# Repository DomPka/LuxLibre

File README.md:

<!-- SPDX-License-Identifier: CC-BY-SA-4.0 -->
<picture>
  <source media="(prefers-color-scheme: dark)" srcset="docs/img/luxlibre_banner_dark.png">
  
</picture>

# LuxLibre

<p align="center"><b>
<a href="#pick-a-light">Pick a light</a> &nbsp;·&nbsp;
<a href="docs/comparison.md">Compare</a> &nbsp;·&nbsp;
<a href="#in-your-browser">Web apps</a> &nbsp;·&nbsp;
<a href="docs/firmware/README.md">Firmware</a> &nbsp;·&nbsp;
<a href="docs/README.md">Design your own</a> &nbsp;·&nbsp;
<a href="hardware/flashka-keychain-v07/FlashKa_v0.7_Build_Guide.pdf">Build a FlashKa</a> &nbsp;·&nbsp;
<a href="#repository-map">Repository map</a> &nbsp;·&nbsp;
<a href="CONTRIBUTING.md">Help</a>
</b></p>

**Open-source flashlights, from the first requirement to the finished light.** LuxLibre is one firmware for many
lights, a set of design rules, a guide to choosing parts and testing them, and seven reference designs: the FlashKa
keychain light and the EDCO family of sealed everyday-carry lights. Every design comes with CAD, dimensioned
drawings, renders, a firmware board header and simulated light output. Anyone may build, change and sell lights
made with it, companies included ([LICENSING.md](LICENSING.md)).

## Pick a light

<picture>
  <source media="(prefers-color-scheme: dark)" srcset="docs/img/lineup_dark.png">
  
</picture>

*All seven at true scale (render). The [web site](https://dompka.github.io/LuxLibre/) has the same lineup: pick a
light there to see its details.*

<table>
<tr>
<td width="33%" valign="top">

<h3><a href="hardware/flashka-keychain-v07/README.md">FlashKa v0.7</a></h3>
<b>Keychain light with a laser and a Bluetooth presenter mode.</b><br>
99.2 × 20 × 18 mm · one 14500<br>
about 1,045 lm · 162 m throw · 2 h 17 min from turbo<br>
<sub><a href="hardware/flashka-keychain-v07/FlashKa_v0.7_Build_Guide.pdf">build guide</a> · <a href="hardware/flashka-keychain-v07/cad/FlashKa_tray_drawing.pdf">drawings</a> · <a href="https://dompka.github.io/LuxLibre/flashka/flashka-app.html">web app</a></sub>
</td>
<td width="33%" valign="top">

<h3><a href="hardware/edco-prism/README.md">EDCO Prism</a></h3>
<b>A beam that is white or any colour.</b><br>
Ø28 × 83 mm · one 18350<br>
about 1,250 lm turbo · red, green, blue and any mix<br>
<sub><a href="hardware/edco-prism/cad/EDCO_Prism_body_drawing.pdf">drawing</a> · <a href="hardware/edco-prism/cad/">CAD</a> · <a href="https://dompka.github.io/LuxLibre/luxlibre/">settings page</a></sub>
</td>
<td width="33%" valign="top">

<h3><a href="hardware/edco-mini/README.md">EDCO Mini</a></h3>
<b>Sealed keychain light with red and UV side lights.</b><br>
Ø22 × 73.5 mm (16340) or Ø19 × 69.4 mm<br>
about 950 lm · keyring tab · magnet version<br>
<sub><a href="hardware/edco-mini/cad/EDCO_Mini-16_body_drawing.pdf">drawings</a> · <a href="hardware/edco-mini/cad/">CAD</a> · <a href="firmware/boards/edco-mini-16/board.h">firmware</a></sub>
</td>
</tr>
<tr>
<td width="33%" valign="top">

<h3><a href="hardware/edco-v02/README.md">EDCO v0.2</a></h3>
<b>The bright one: an SST-40 at up to 5.7 A.</b><br>
Ø26 × 97.8 mm (18500) or Ø22 × 95.6 mm (14500)<br>
about 1,760 lm · USB-C under a twist collar<br>
<sub><a href="hardware/edco-v02/cad/EDCO-18_body_drawing.pdf">drawings</a> · <a href="hardware/edco-v02/cad/">CAD</a> · <a href="firmware/boards/edco-v02-18/board.h">firmware</a></sub>
</td>
<td width="33%" valign="top">

<h3><a href="hardware/edco-v01/README.md">EDCO v0.1</a></h3>
<b>A plain sealed tube with USB-C in the tail.</b><br>
Ø20 × 93.5 mm · one 14500<br>
about 966 lm · 2 h 21 min from turbo<br>
<sub><a href="hardware/edco-v01/cad/EDCO_body_drawing.pdf">drawing</a> · <a href="hardware/edco-v01/cad/">CAD</a> · <a href="firmware/boards/edco-v01/board.h">firmware</a></sub>
</td>
<td width="33%" valign="top">
<a href="docs/comparison.md"><picture><source media="(prefers-color-scheme: dark)" srcset="docs/img/compare_light_dark.png"></picture></a>
<h3><a href="docs/comparison.md">Compare them</a></h3>
<b>Every design against 14 popular lights</b>, from the RovyVon A3 Pro to the Fenix PD36R Pro: light, throw,
runtime, size and price, with sources.
</td>
</tr>
</table>

*Every picture is a render made from the design files. None of these lights has been built yet: every light figure
is simulated with the LuxLibre simulator (out of the front, LED at 85 °C) or estimated, and every page says
which.*

## Where to go next

| I want to | Go to |
|---|---|
| see how the designs compare with lights I can buy | [docs/comparison.md](docs/comparison.md) |
| look at a design in detail: specifications, renders, how it is built, cost, open points | the design pages above, or [all the lights](hardware/README.md) |
| get drawings and CAD to make parts | each design's `cad/` folder: STEP files and A3 drawings (DXF, PDF, PNG), e.g. [EDCO Prism](hardware/edco-prism/cad/README.md), [FlashKa v0.7](hardware/flashka-keychain-v07/cad/README.md) |
| try the FlashKa control app without a light | the [FlashKa web app](https://dompka.github.io/LuxLibre/flashka/flashka-app.html), *Try demo mode* |
| change the settings of a LuxLibre light from the browser | the [LuxLibre settings page](https://dompka.github.io/LuxLibre/luxlibre/) (Web Serial over USB-C; demo mode without a light) |
| run the firmware without hardware | [Quick start](#quick-start) and [docs/firmware/simulator.md](docs/firmware/simulator.md) |
| design my own light | [docs/README.md](docs/README.md): requirement sheet, choosing parts, design rules, testing |
| put LuxLibre on my board | [docs/firmware/porting.md](docs/firmware/porting.md) |
| build a FlashKa | the [build guide](hardware/flashka-keychain-v07/FlashKa_v0.7_Build_Guide.pdf) and [order files](hardware/flashka-keychain-v07/order_files/README.txt) |
| report a build, measurements or a problem | [CONTRIBUTING.md](CONTRIBUTING.md) and the [build report form](https://github.com/DomPka/LuxLibre/issues/new?template=build_report.yml) |

## The lights at a glance

| Light | Size (mm) | Cell | Light at 30 s | After 10 min | Throw | From turbo to the end point | What sets it apart |
|---|---|---|---|---|---|---|---|
| [FlashKa v0.7](hardware/flashka-keychain-v07/README.md) | 99.2 × 20 × 18 | 14500, 1,500 mAh | 966 lm | about 280 lm | 6,605 cd, 162 m | 2 h 17 min | Class 2 laser, Bluetooth presenter mode, glowing key ring |
| [EDCO Prism](hardware/edco-prism/README.md) | Ø28 × 83.0 | 18350, 1,200 mAh | 1,248 lm | about 280-350 lm | about 3,000 cd (est.) | 1 h 29 min | colour beam, RGB-lit button, settings page over USB-C |
| [EDCO Mini-16](hardware/edco-mini/README.md) | Ø22 × 73.5 | 16340, 650 mAh | 944 lm | about 230 lm | about 11,000 cd (est.) | 1 h 07 min | red and UV side lights, keyring tab, magnets in the M version |
| [EDCO Mini-14](hardware/edco-mini/README.md) | Ø19 × 69.4 | 14350 made to order, about 400 mAh | 978 lm | about 195 lm | about 5,600 cd (est.) | 51 min | the smallest; needs a cell made to order |
| [EDCO-18](hardware/edco-v02/README.md) | Ø26 × 97.8 | 18500, 1,500 mAh | 1,759 lm | about 330-390 lm | about 18,000 cd (est.) | 1 h 39 min | the brightest; USB-C under a twist collar |
| [EDCO-14](hardware/edco-v02/README.md) | Ø22 × 95.6 | 14500, 1,000 mAh | 1,561 lm | about 260-320 lm | about 11,000 cd (est.) | 1 h 18 min | the same in a slimmer body |
| [EDCO v0.1](hardware/edco-v01/README.md) | Ø20 × 93.5 | 14500, 1,500 mAh | 966 lm | about 290 lm | 6,605 cd, 162 m | 2 h 21 min | sealed USB-C socket in the tail |

All figures are simulated, out of the front, with the LED at 85 °C in 25 °C still air. "est." marks an estimate
from the optic's beam angle. The end point is ANSI FL1: 10 % of the 30 s output.

## Against popular flashlights

<picture>
  <source media="(prefers-color-scheme: dark)" srcset="docs/img/compare_light_dark.png">
  
</picture>

* **Keychain size.** The EDCO Mini gives more than twice the light of a 60 mm RovyVon A3 Pro at 30 s. The best
  16340 lights, the Olight Baton 4 and Fenix E18R V2.0, are shorter and still brighter.
* **14500 and 18350 size.** EDCO-18 and EDCO-14 are the brightest at 30 s and run the longest from turbo, but
  they are about 17-20 mm longer than the Skilhunt MiX-7 or Emisar D3AA.
  * EDCO Prism gives about 10 % less white than the MiX-7, the only other colour-beam light of its size. It runs
    longer and charges from any USB-C cable.
* **18650 size** is still the territory of lights like the Fenix PD36R Pro: no LuxLibre design is that big yet.

Every number, its source and what was left out: [docs/comparison.md](docs/comparison.md). The other lights were
measured by independent reviewers; the LuxLibre lights are simulated, and their measured numbers will replace these
once they are built.

## In your browser

| Page | What it does | Needs |
|---|---|---|
| **[LuxLibre settings page](https://dompka.github.io/LuxLibre/luxlibre/)** | reads and changes every parameter of a LuxLibre light over USB-C (Web Serial), and for the EDCO Prism the beam's colour and the custom colour; a demo mode with the EDCO Prism's settings | Chrome or Edge on a computer and a USB-C data cable |
| **[FlashKa control app](https://dompka.github.io/LuxLibre/flashka/flashka-app.html)** | battery, temperature and runtime; light on and off, levels and exact current; profiles with an editor; presenter settings and paired computers; a demo mode with a simulated light | Chrome or Edge on Android, Windows, macOS or ChromeOS; Bluefy on iPhone and iPad |
| **[FlashKa firmware installer](https://dompka.github.io/LuxLibre/flashka/flashka-flasher.html)** | writes the firmware through the light's USB-C port and checks what it wrote; the firmware image is inside the page | Chrome or Edge on a computer and a USB-C data cable |

All three run entirely in the browser: nothing is uploaded and there is no account. The
[start page](https://dompka.github.io/LuxLibre/) links them all. They are published from [site/](site/) and
[hardware/flashka-keychain-v06/app/](hardware/flashka-keychain-v06/app/) with GitHub Pages.

## Repository map

| Folder | What is in it | Start with |
|---|---|---|
| [hardware/](hardware/README.md) | the lights: design pages, CAD and drawings, renders, circuit boards, order files | [the lights](hardware/README.md) |
| &nbsp;&nbsp;[flashka-keychain-v07/](hardware/flashka-keychain-v07/README.md) | FlashKa v0.7, the keychain light with a laser and a presenter mode | [build guide](hardware/flashka-keychain-v07/FlashKa_v0.7_Build_Guide.pdf), [drawings](hardware/flashka-keychain-v07/cad/README.md) |
| &nbsp;&nbsp;[edco-prism/](hardware/edco-prism/README.md) | EDCO Prism, white or any-colour beam | [drawing](hardware/edco-prism/cad/README.md), [pictures](hardware/edco-prism/assets/README.md) |
| &nbsp;&nbsp;[edco-mini/](hardware/edco-mini/README.md) | EDCO Mini-16 and Mini-14, sealed keychain lights | [drawings](hardware/edco-mini/cad/README.md), [pictures](hardware/edco-mini/assets/README.md) |
| &nbsp;&nbsp;[edco-v02/](hardware/edco-v02/README.md) | EDCO-18 and EDCO-14, about 1,760 lm | [drawings](hardware/edco-v02/cad/README.md), [pictures](hardware/edco-v02/assets/README.md) |
| &nbsp;&nbsp;[edco-v01/](hardware/edco-v01/README.md) | EDCO v0.1, the first EDCO | [drawing](hardware/edco-v01/cad/README.md), [pictures](hardware/edco-v01/assets/README.md) |
| &nbsp;&nbsp;[flashka-keychain-v06/](hardware/flashka-keychain-v06/README.md), [v05/](hardware/flashka-keychain-v05/README.md) | older FlashKa designs; v0.6 also holds the FlashKa firmware and web pages | |
| &nbsp;&nbsp;[tools/](hardware/tools/README.md) | scripts for the drawings, animations, lineup and banner | |
| [firmware/](firmware/README.md) | the LuxLibre firmware source: core, ports, board headers, tests, simulator | [firmware guide](docs/firmware/README.md), [board headers](firmware/boards/README.md) |
| [docs/](docs/README.md) | design rules, choosing parts, flashlight types, testing, the comparison, the firmware guide | [reading paths](docs/README.md) |
| [tools/](tools/README.md) | `lux_calc.py` (runtime, throw, heat, trace width, NTC...) and the comparison charts | |
| [templates/](templates/README.md) | requirement sheet, design log, decision matrix, BOM, review checklist, test report | [requirement sheet](templates/requirements.md) |
| [site/](site/README.md) | the web site: start page and LuxLibre settings page | [live site](https://dompka.github.io/LuxLibre/) |

At the top level: [CHANGELOG](CHANGELOG.md), [CONTRIBUTING](CONTRIBUTING.md), [SAFETY](SAFETY.md),
[SECURITY](SECURITY.md), [LICENSING](LICENSING.md) (what the licences mean), [TRADEMARKS](TRADEMARKS.md) and the
[licence texts](LICENSES/). Every page has a path at the top (LuxLibre › Lights › EDCO Prism) to find your way back.

## Quick start

**Try the web pages without a light:** open the
[settings page](https://dompka.github.io/LuxLibre/luxlibre/) or the
[FlashKa control app](https://dompka.github.io/LuxLibre/flashka/flashka-app.html) and choose the demo mode.

**Try the LuxLibre firmware without hardware** (Linux, macOS, or Windows with WSL):

```sh
cd firmware
make test                                    # unit and behaviour tests
make sim BOARD=edco-prism                    # the simulator with the EDCO Prism's board header
build/luxsim-edco-prism --preset board "2C W600000"            # double click for turbo, then 10 minutes
build/luxsim-edco-prism --preset board "5C W2000 2C W2000"     # colour beam on, then the next colour
make sim BOARD=edco-mini-16                  # the same for any board in firmware/boards/
build/luxsim-edco-mini-16 --preset board --set TURBO_S=0 "2C W600000"
```

<picture>
  <source media="(prefers-color-scheme: dark)" srcset="docs/img/thermal-regulation-dark.png">
  
</picture>

*The LuxLibre firmware in its simulator: turbo, then smooth thermal regulation at 50 °C for a keychain light and an
18650 light ([how this was made](docs/firmware/simulator.md)).*

**Design a light:** start with the requirement sheet ([templates/requirements.md](templates/requirements.md)), then
follow [docs/choosing-parts.md](docs/choosing-parts.md) and check the result against
[docs/design-rules.md](docs/design-rules.md). [docs/README.md](docs/README.md) suggests a reading order.

**Put LuxLibre on your board:** [docs/firmware/porting.md](docs/firmware/porting.md).

**Build a FlashKa:** read the [build guide](hardware/flashka-keychain-v07/FlashKa_v0.7_Build_Guide.pdf) once from
start to end, then use the files in [order_files/](hardware/flashka-keychain-v07/order_files/README.txt).

## Status

LuxLibre 0.5.0. What has been tested so far:

| Part | State |
|---|---|
| LuxLibre firmware core | 13 unit tests with 529 checks, and 47 behaviour tests with 263 checks in the simulator on three test boards; all run by CI |
| ATtiny1616 and CH32V003 ports | build and link in CI; not yet run on hardware |
| ESP32-C3 port | built with ESP-IDF 5.3.1 in CI for every FlashKa and EDCO board header; not yet run on hardware |
| LuxLibre settings page | checked in a browser in demo mode and against a simulated serial port; not yet used with a real light |
| FlashKa v0.7 | designed and checked by software: netlist across both boards, KiCad DRC with 0 errors, both boards' 3D models inside the housing, key travel, drawings against the CAD, both casting moulds, cost; light output and runtime simulated; not yet built |
| FlashKa firmware and web pages (0.7.0 for v0.7, 0.6.0 for v0.6) | 166 unit and 9 thermal simulation tests (v0.7 build), 153 host tests (v0.6 build); control app, installer and start page checked in a browser against simulated hardware; not yet run on a real light |
| EDCO Prism, Mini, v0.2 and v0.1 | concepts. Each housing is modelled in CadQuery and checked for fits, walls and interference. The body drawings are checked against the solids. Each has a firmware board header, and its light output, temperatures and runtime are simulated. The circuit boards are not drawn yet, and nothing has been built |
| Design rules, guides, tools | complete; numbers from standards and datasheets carry sources |

The first hardware results will be added as test reports. Measurements from your builds are the most valuable
contribution: the [build report](https://github.com/DomPka/LuxLibre/issues/new?template=build_report.yml) issue
form asks for exactly what is needed. See [CONTRIBUTING.md](CONTRIBUTING.md).

## Safety and security

Lithium cells, bright LEDs, hot surfaces and lasers can hurt people. Read [SAFETY.md](SAFETY.md) before building or
testing. Security problems (for example in Bluetooth pairing or the web pages) are reported privately as described
in [SECURITY.md](SECURITY.md).

## Licences

Like ArduPilot, LuxLibre may be used, changed, built and sold by anyone, companies included, as long as the shared
parts stay open:

- firmware and tools: [GPL-3.0-or-later](LICENSES/GPL-3.0-or-later.txt)
- hardware design files: [CERN-OHL-W-2.0](LICENSES/CERN-OHL-W-2.0.txt)
- documentation: [CC-BY-SA-4.0](LICENSES/CC-BY-SA-4.0.txt)
- the FlashKa Rust firmware, web pages and web tools: MIT or Apache-2.0

What that means in practice, including for products you sell: [LICENSING.md](LICENSING.md). How to use the names
LuxLibre and FlashKa: [TRADEMARKS.md](TRADEMARKS.md).

## Background

LuxLibre stands on the shoulders of the enthusiast flashlight community:

* The [Anduril](https://github.com/ToyKeeper/anduril) firmware (GPL-3.0) showed how much a single button can do.
* Early open lights such as the
  [HexBright](https://techcrunch.com/2011/07/06/kid-tested-grant-imahara-approved-hexbrite-open-source-flashlight)
  showed that people want to change their lights.
* The community keeps asking for exact levels, visible settings and configuration without a command line
  ([BLF discussion, 2026](https://budgetlightforum.com/t/hey-folks-i-want-to-drag-flash-lights-into-2026/234210)).

LuxLibre adds what a design team needs around the firmware: rules, a part-selection method, tests, a simulator
and complete reference designs. Its parameter system and its licensing follow ArduPilot.

The name: Latin *lux*, light, and *libre*, free as in freedom.

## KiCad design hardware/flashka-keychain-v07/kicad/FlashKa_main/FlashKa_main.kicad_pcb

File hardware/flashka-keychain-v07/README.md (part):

<!-- SPDX-License-Identifier: CC-BY-SA-4.0 -->
[LuxLibre](../../README.md) › [Lights](../README.md) › FlashKa Keychain v0.7

# FlashKa Keychain v0.7

**On this page:** [What's new in v0.7](#whats-new-in-v07) · [Specifications](#specifications) · [Gallery](#gallery) · [Web app and firmware installer](#web-app-and-firmware-installer) · [Presenter mode](#presenter-mode) · [Building one](#building-one) · [Cost](#cost) · [What has been checked](#what-has-been-checked) · [Known limitations](#known-limitations) · [Firmware](#firmware-two-options) · [What is in this folder](#what-is-in-this-folder) · [Licences](#licences)

FlashKa is LuxLibre reference design #1: a 99.2 × 20 × 18 mm aluminium keychain light. Version
0.7 is the **1000 lm FlashKa**: a Luminus SST-20 Gen 2 LED behind a LEDiL TIR optic, driven by a
4 A buck converter at up to 2,850 mA, gives about 1,045 lm (G1 bin) out of the front at switch-on
and about 160 m of throw (both simulated), then holds about 600 lm on High for about three and a
half minutes and about 280 lm until the battery runs low, about 2 h 17 min from turbo. It keeps
what made FlashKa a FlashKa: a 3 mA moonlight, a Class 2 green laser behind a hardware safety
switch, USB-C charging, Bluetooth and a **presenter mode** in which the light is a Bluetooth
keyboard that turns your slides. One 14500 Li-ion cell (Vapcell INR14500 F15, 1,500 mAh) is
protected on the main board and charges at about 500 mA. The three keys sit on the centre line of
the bottom face: a clear acrylic main key whose frosted ring glows in the ring colour, and two
black rubber keys whose chevrons point along the light, **^** next and **v** previous. The switches
sit on a small key board that talks to the main board through six gold spring contacts. No part of
the light is 3D-printed, there is no marking on it, and the aluminium body is a faceted octagon
with textured panels. It runs FlashKa firmware 0.7.0, the v0.7 build of the FlashKa firmware.

*Render — FlashKa has not been built yet.*

> **Status: designed, not yet built.** Everything here has been checked by software (see
> [What has been checked](#what-has-been-checked)), but nobody has assembled a FlashKa yet, and
> every picture of the light is a render. The light figures are simulated from the LED and optic
> datasheets, not measured. The first build must follow the bring-up in the LuxLibre testing
> guide, [docs/testing.md](../../docs/testing.md#bring-up-of-a-new-board), and the plans in the
> [firmware document](../flashka-keychain-v06/docs/firmware.md#7-verification-status), sections 7
> and 9.9, before more are made. The light holds a lithium cell and a laser: read
> [SAFETY.md](../../SAFETY.md) first.

## What's new in v0.7

* **About 1000 lm and 160 m of throw.** The owner asked for at least 1000 lm and about 100 m of
  throw, like the RovyVon Aurora A2. The LED is now an SST-20 **Gen 2** (more light per amp) under
  a **LEDiL LISA3-RS-PIN TIR optic** (20° beam, 87 % efficiency, LEDiL's data). Turbo runs at
  2,850 mA: about 1,045 lm out of the front at switch-on and 966 lm with the LED at 85 °C, the
  datasheet's reference; 6,605 cd and 162.5 m at switch-on (all simulated). The optic is also the
  front window: the glass window and the plastic spacer ring are gone.
* **A long higher output.** High (1,530 mA, about 601 lm) runs for about 210 s at full output in
  25 °C still air; then a temperature regulator holds the light at about 280 lm with the body at
  about 46 °C (simulated). Full turbo lasts about 58 s. The profile's temperature limit (50 °C) is
  the regulator's set point: full output until the light gets there, then it holds it.
* **A stronger driver with board protection.** A TI TPS62095 4 A buck (100 % duty mode) in the
  same current loop, full scale 3,552 mA; the firmware never asks for more than 3.0 A, the LED's
  maximum. The cell has no protection board, so a DW01A protection IC and a dual MOSFET in the
  cell minus (net BATN) protect it on the main board; the IC reads the MOSFETs' drop on its own
  tracks (Kelvin sensing). After a trip the light stays off until USB is plugged in.
* **One 14500 cell.** A Vapcell INR14500 F15 Li-ion cell (1,500 mAh typical, 1,150 mAh minimum,
  3 A, 14.0 × 49.0 mm, flat top) instead of the two small pouch cells of the earlier layout: more
  than twice the capacity, about 137 min from turbo to the low-voltage step-down (simulated).
  Nickel strips are spot-welded to its ends, or you buy it with welded tabs; never solder onto the
  cell. It charges at about 500 mA (a full charge in about 3.5 h). One cell sags under the turbo
  current, so **turbo dims as the cell empties**: 966 lm from a full cell, 948 lm at 90 %, 916 lm
  at 75 %, 775 lm at half charge and 651 lm at 25 % (30 s after switching on, LED at 85 °C,
  simulated). The bay takes any flat-top 14500 up to 14.5 × 50.4 mm; a high-drain cell such as the
  Vapcell K10 (1,000 mAh, 8 A) sags less and keeps full turbo to a lower charge (not simulated),
  with about a third less runtime.
* **A faceted octagon.** The body is 20 × 18 mm with eight flat facets (bottom and top 13.2 mm,
  sides 11.2 mm, diagonals 4.8 mm) instead of the 20 × 16 mm rectangle: the same 99.2 mm length
  (within the owner's 99.4 mm limit), the same textured panels and grooves. The lid is a 3.4 mm cap
  over the top and the two upper diagonal facets, held by four M1.6 × 6 screws; its joint follows a
  facet edge.
* **Firmware 0.7.0.** The same firmware code, built for the v0.7 board: new levels and profiles,
  a 2,850 mA turbo for at most 60 s, a temperature regulator, the F15's capacity and voltage
  curve, a 2.8 A cell-current limit. The installer asks which FlashKa you have, and the app
  recognises the board ([Firmware](#firmware-two-options)).
* **Keys on the centre line.** ^ next, ● main and v previous sit in one shallow frame in the
  middle of the bottom face, a little below its surface, so a table cannot press them. The main
  key is clear polished acrylic (PMMA); its frosted ring carries the light of the two ring LEDs.
  The side keys are black urethane rubber with a raised chevron along the light and a stainless
  stiffener, so they click wherever you press them. Held like a presenter (head towards the
  screen), the key nearest the head shows **^** (next) and the key nearest your hand **v**
  (previous).
* **A key board with pogo pins.** The switches and ring LEDs moved to a 19.0 × 14.8 mm board
  screwed to the floor. Six gold pogo pins press on six pads of the main board: no cable, nothing
  to plug in ([chapter 14, section 14.2.2](docs/ch14_v0.7_keys_and_skin.md#1422-a-key-board-under-the-main-board)).
* **One panel at JLCPCB.** Both boards come in one panel with black solder mask: one order, one
  set of upload files.
* **Premium materials, and a rugged skin.** Anodised 6061-T6, cast PMMA, POM-C, urethane rubber
  and stainless steel. The facets frame recessed panels with a diagonal V texture, and grooves
  ring the head and the tail. No writing at all; the laser set screw hides under the lid. The laser
  warning label is printed in the build guide (section 1, *Laser safety*) and goes on the
  packaging; an optional lid label is included for lights that are sold or given away.
* **Compared with the RovyVon Aurora A2**, beam for beam and size for size ([below](#compared-with-the-rovyvon-aurora-a2)).
* **Lower cost.** Since the first v0.7 layout one light costs 59.61 USD less (918.89 → 859.28 USD)
  and each of five 11.89 USD less, although the optic, the driver, the protection and the bigger
  cell were added: a printed resin casting mould instead of an aluminium one, a cheaper casting
  rubber of the same hardness, one merged parcel from JLCCNC and JLC3DP that stays below the EU's
  150 EUR customs line, no window and no spacer ring, a cheaper LED board. The one-cell octagon
  itself costs 4.47 USD more for one light and 4.35 USD less per light for five ([Cost](#cost)).

## Specifications

| Item | Value |
|---|---|
| Size and mass | 99.2 × 20 × 18 mm, a faceted octagon (eight flat facets). Aluminium tray + lid 30.9 g, all housing parts together 32.7 g, 32.8 g with the optional laser sleeve (both calculated from the CAD solids). About 62 g with the optic, the cell (about 22 g) and the electronics (an estimate, not weighed) |
| LED and optic | Luminus SST-20 Gen 2, 6500 K, G1 bin, on a 10 mm copper DTP board, under a LEDiL LISA3-RS-PIN TIR optic (Ø10.0 × 6.9 mm, pins cut off, glued into the head bore; LEDiL's simulated data for this LED: 20° beam, 87 % efficiency, 5.5 cd per LED lumen). No front window: the optic's face sits 0.2 mm behind the front face |
| Light output | **Not measured yet.** Simulated with the firmware 0.7.0 thermal model, the LED datasheet and the optic data (25 °C still air, full cell, default profile): turbo 2,850 mA gives **about 1,045 lm out of the front at switch-on** (1,201 lm at the LED, G1 bin) and 1,019 lm at 30 s; with the LED at 85 °C, the datasheet's reference, 966 lm. Full turbo for about 58 s, then the temperature regulator. High 1,530 mA: about 601 lm (655 lm at switch-on) for about 210 s. Then about 280 lm sustained (281 lm with the LED taken at 85 °C, 296 lm with its simulated temperature; 325 lm after 10 min). Turbo dims as the cell empties: 775 lm from a half-full cell (LED at 85 °C). Peak **6,605 cd, 162.5 m** ANSI throw at switch-on (6,110 cd and 156.3 m with the LED at 85 °C). Runtime from turbo: 137 min to the ANSI end point (here the low-voltage step-down), off after about 235 min; a cell at the maker's minimum capacity runs about 23 % shorter ([sources](assets/v07/sources_comparison.md), [firmware document, section 9](../flashka-keychain-v06/docs/firmware.md#9-flashka-keychain-v07-firmware-070)) |
| LED driver | TI TPS62095 4 A synchronous buck (100 % duty mode) in a current loop (TLV333 op-amp, 20 mΩ sense resistor); full scale 3,552 mA. Built-in levels from 2 mA (moonlight in the Endurance profile; 3 mA by default) to the 2,850 mA turbo; the firmware caps every request at 3,000 mA |
| Battery | One Vapcell INR14500 F15 Li-ion cell, 14.0 × 49.0 mm, flat top, no protection board: 1,500 mAh typical, 1,150 mAh minimum (maker's data, at 0.2C), 3.60 V, 3 A maximum continuous, about 22 g. Nickel strips spot-welded to both ends (or a cell with welded tabs), one 24 AWG wire to each J2 pad. The firmware's estimates use 1,400 mAh. Any flat-top 14500 up to 14.5 × 50.4 mm fits; for full turbo to a lower charge a high-drain cell such as the Vapcell INR14500 K10 (1,000 mAh, 8 A; not simulated) |
| Protection | on the main board: DW01A protection IC and SE8830A dual MOSFET in the cell minus, Kelvin-sensed (the IC reads only the MOSFETs' drop); over-current trip 5.3-5.6 A typical at 25 °C and 4.3-4.5 A with hot MOSFETs, as low as 3.0-3.15 A in the worst case; the firmware keeps its estimate of the cell current at or below 2.8 A: 93 % of the F15's 3 A rating (a documented deviation from LuxLibre rule BAT-1, only in turbo) and 7-12 % below the worst-case trip. After a trip the light stays off until USB is plugged in |
| Keys | On the centre line of the bottom face, in a 0.5 mm deep frame, 18.65 / 25.65 / 32.65 mm from the front: ^ next and v previous, black cast urethane rubber (Shore A 80), 4.2 × 10.0 mm, raised chevron along the light, glued-in stainless stiffener; ● main, clear cast PMMA, 6.8 × 6.8 mm, frosted ring. Faces 0.15 mm (main) and 0.30 mm (side) below the bottom face. Alps SKRKAEE020 switches (click at 1.6 N) |
| Ring | Two RGB LEDs (NH-B1010RGBT-HF) shine into the clear main key; its frosted ring glows. Patterns: [firmware.md](../flashka-keychain-v06/docs/firmware.md#25-ring-colours), section 2.5 |
| Key board | 19.0 × 14.8 mm, 4 layers, 0.8 mm, ENIG, screwed to the floor with two M1.6 × 2.5 screws; six Harwin P70-1010045R pogo pins press on six gold pads of the main board |
| Laser | 520 nm module, Class 2 (≤ 1 mW), slide-switch interlock S2 in its supply. No marks on the body: towards the head is SAFE, towards the tail ARM |
| Charging | USB-C (two 5.1 kΩ CC resistors), TP4057 linear charger, about 500 mA (494 mA, the F15's standard charge; a full charge in about 3.5 h), through the protection MOSFETs; status on the ring. With a nearly empty cell the charger warms the board next to the temperature sensor and charging pauses above 45 °C until it cools to 43 °C: normal, not a fault |
| Brain | ESP32-C3-MINI-1 module (Bluetooth LE, USB serial/JTAG) |
| Bluetooth and presenter mode | One connection at a time; the name is `FlashKa-XXXX`; protocol version 2 ([ble_protocol.md](../flashka-keychain-v06/docs/ble_protocol.md)). Presenter mode is a Bluetooth LE keyboard, LE Secure Connections "Just Works", up to 4 computers, about 20 mA while it is on (estimate) |
| Circuit boards | Main board 24 × 16.5 mm (the v0.6 outline) with the new power stage, and the key board: one JLCPCB panel of 45.0 × 32.5 mm, 4 layers, 0.8 mm, ENIG, black solder mask. JLCPCB assembles 79 parts of 35 kinds, on both sides of both boards |
| Housing | CNC-machined 6061-T6 tray and lid (JLCCNC), a faceted octagon, bead-blasted and black anodised, recessed textured panels, no marking; the lid is a 3.4 mm cap held by four M1.6 × 6 screws; the laser set screw (M1.6 × 5) sits under the lid. The cell lies on two floor rails, held by foam. PMMA main keys and black POM-C parts as two machining kits (JLCCNC). Side keys cast at home in a resin mould that JLC3DP prints once per builder (an aluminium mould is the durable option) |
| Firmware | FlashKa firmware 0.7.0 for the v0.7 board (`flashka-fw-v0.7.0-merged.bin`); the firmware, the installer and the app are in the [v0.6 folder](../flashka-keychain-v06/README.md), which builds both boards' firmware |

### Levels (firmware 0.7.0)

Lumens are estimated light out of the front with the LED at 85 °C (the LED datasheet × the
optic's 87 %); a cool LED gives up to about 8 % more in the first seconds. The profile is chosen in
the app.

| Profile | Moonlight | Low | Medium | High | Turbo | Temperature limit (held) | Low-voltage step-down | Cell current limit |
|---|---|---|---|---|---|---|---|---|
| Balanced (default) | 3 mA, ~1 lm | 40 mA, 19 lm | 250 mA, 119 lm | 1,530 mA, 601 lm | 2,850 mA, 966 lm, at most 60 s, then High | 50 °C | 3.20 V | 2,800 mA |
| Extreme | 3 mA, ~1 lm | 50 mA, 24 lm | 400 mA, 187 lm | 1,800 mA, 683 lm | 2,850 mA, 966 lm, at most 60 s, then High | 50 °C | 3.15 V | 2,800 mA |
| Endurance | 2 mA, ~1 lm | 15 mA, 7 lm | 100 mA, 48 lm | 500 mA, 230 lm | none | 47 °C | 3.25 V | 800 mA |

The temperature limit is the set point of a regulator: the light keeps full output until the
temperature it predicts 8 s ahead reaches the limit, then holds its sensor just below it. In 25 °C
still air turbo holds full output for about 58 s (the 60 s timer then ends it) and High for about
210 s; both then settle at about 280 lm with the body (the surface in your hand) at about 46 °C.
One Li-ion cell sags under the turbo current, so **turbo dims as the cell empties**: 30 s after
switching on it gives 966 lm from a full cell, 948 lm at 90 % charge, 916 lm at 75 %, 775 lm at
50 % and 651 lm at 25 % (LED at 85 °C); High keeps its full 601 lm down to about 15 %. The
low-voltage step-down (under load) drops the light to Low when the cell is nearly empty, about
137 min after a turbo start in the default profile. Endurance High (230 lm) never steps down for
heat (simulated, [firmware document, sections 9.6](../flashka-keychain-v06/docs/firmware.md#96-simulated-behaviour-25-c-still-air)
and [9.11](../flashka-keychain-v06/docs/firmware.md#911-thermal-regulator-v07)).

## Gallery

All pictures are renders made from the design files.

|  |  |
|---|---|
| **Bottom face.** v previous, ● main with its frosted ring (lit cyan) and ^ next, on the centre line in one frame. The head is at the upper right. | **The keys.** Clear PMMA main key (the switch shows through it) between the two rubber keys. The chevrons point along the light: the one nearest the head to the head (next), the other to the tail (previous). |
|  |  |
| **Control side.** The USB-C opening, the facets and textured panels, the lid with its radio-window insert and four screws. | **Laser side.** The slot of the slide switch S2 near the head. No marks: towards the head is SAFE, towards the tail ARM. |
|  |  |
| **Lid.** Three textured panels and the textured POM-C radio-window insert over the antenna. | **Front.** The laser module and the TIR optic, set 0.2 mm into the head, with the LED behind it. |
|  |  |
| **Without the lid.** The real routed board, the hold-down pads, the S2 slide switch, the 14500 cell on its two rails and the lanyard slot. | **Exploded view.** Lid, the cell with its nickel strips, main board, key board with its pogo pins, keys and the parts of the head. |
|  |  |
| **Every part, labelled.** | **Casting mould.** The printed resin mould; four keys per pour. The stainless plate and doubler are glued into each key. |

## Compared with the RovyVon Aurora A2

*Render. FlashKa: simulated, not yet built. RovyVon Aurora A2: maker's data and the
[1lumen measurement](https://1lumen.com/review/rovyvon-a2/). Every number and its source:
[sources_comparison.md](assets/v07/sources_comparison.md).*

| | FlashKa v0.7 (simulated) | RovyVon Aurora A2 (measured by 1lumen, Gen 3) |
|---|---|---|
| Light out of the front at switch-on | 1,045 lm (966 lm with the LED at 85 °C) | 633 lm (maker: 650 lm) |
| After 30 s | 1,019 lm | 394 lm |
| After 10 minutes | 325 lm | 118 lm |
| Peak intensity / throw | 6,605 cd / 162.5 m | 3,775 cd / 123 m |
| Size | 99.2 × 20 × 18 mm | 57.3 × Ø15.6 mm |
| Mass | about 62 g (estimate) | 19.5 to 33.9 g |
| Battery | 1,500 mAh (one 14500 cell) | 300 mAh |
| Runtime from turbo to the ANSI end point | 137 min | 1 h 04 min |
| Extras | Class 2 laser, Bluetooth slide remote, app | none listed |

With the TIR optic FlashKa out-throws the A2: 162.5 m against 123 m at switch-on, and about
1.65 times its light (calculated). After 30 s it gives about 2.6 times as much (1,019 against
394 lm) and after ten minutes about 2.8 times (325 against 118 lm); it has five times the battery
capacity, runs about twice as long from turbo and adds the laser and the presenter mode. It is longer and
heavier: 99.2 mm against 57.3 mm, about 62 g against 20-34 g. From a half-full cell FlashKa's turbo
gives about 775 lm (LED at 85 °C), still above the A2. The A2's figures are measured, FlashKa's are
simulated; the first build must measure them.

*Light out of the front at 25 °C. FlashKa simulated with turbo (solid) and High (dashed), both
from the default profile; the A2 as the three points 1lumen published.*

## Web app and firmware installer

The web pages serve both FlashKa v0.7 and v0.6. Each page is one HTML file that works offline and
runs entirely in the browser.

| Page | Address on GitHub Pages | File |
|---|---|---|
| Start page | <https://dompka.github.io/LuxLibre/flashka/> | [v0.6 app/index.html](../flashka-keychain-v06/app/index.html) |
| **Control app** | <https://dompka.github.io/LuxLibre/flashka/flashka-app.html> | [v0.6 app/flashka-app.html](../flashka-keychain-v06/app/flashka-app.html) |
| **Firmware installer** | <https://dompka.github.io/LuxLibre/flashka/flashka-flasher.html> | [v0.6 app/flashka-flasher.html](../flashka-keychain-v06/app/flashka-flasher.html) |

The installer holds both firmware images and first asks **"Which FlashKa do you have?"**: choose
**"FlashKa v0.7 - three keys in the middle"**. After connecting it reads the firmware already on
the light, warns if it belongs to the other board and refuses image files made for the other
board: the two firmwares set the LED current with different scales and limits. It writes the
firmware through the USB-C port and needs Chrome or Edge on a computer.

The control app reads from the light whether it is a v0.7 or a v0.6. On a v0.7 it shows the v0.7
profiles, limits a custom turbo to 2,850 mA and shows the estimated lumens next to the current
(for example "1530 mA · 601 lm", marked as estimates). It shows the battery, temperature and
runtime, switches the light, holds the profiles and sets up presenter mode; its demo mode works
without a light and can simulate a v0.7. It needs Chrome or Edge (Bluefy on an iPhone or iPad).
Details: [web_apps.md](../flashka-keychain-v06/docs/web_apps.md).

## Presenter mode

Hold both side keys (^ and v) for 2 s. The ring blinks magenta twice, then breathes cyan while the
light waits for the computer. Hold the light like a presenter, keys up under your thumb and the
head towards the screen: the key nearest the head shows **^** and turns to the next slide, the key
nearest your hand shows **v** and turns back.

| Input | What it does | Key sent |
|---|---|---|
| ^ click | next slide | Page Down (Right Arrow in the "arrows" key set) |
| v click | previous slide | Page Up (Left Arrow in the "arrows" key set) |
| ^ hold 0.8 s | start the show | F5, once |
| v hold 0.8 s | end the show | Esc, once |
| ● click | black screen on or off | B |
| ● hold | laser on while held (S2 must be on ARM) | none |
| ● 4 clicks | lock the light; this also leaves presenter mode | none |
| ^ + v hold 2 s | enter or leave presenter mode | none |
| ^ + v hold 10 s | forget all paired computers (ring white × 3) | none |

In flashlight mode ^ steps one level up and v one level down while the light is on. Pairing works
like a Bluetooth keyboard: no PIN, no app, up to 4 computers. It has not been tried on any real
system yet. The complete user manual is section 2 of the
[firmware document](../flashka-keychain-v06/docs/firmware.md) and Appendix A of the build guide
PDF; the v0.7 levels are in its section 9.3.

## Building one

1. Read [FlashKa_v0.7_Build_Guide.pdf](FlashKa_v0.7_Build_Guide.pdf) from start to end once. It is
   written for people without electronics experience; the source is
   [docs/build_guide_v0.7.md](docs/build_guide_v0.7.md).
2. Upload the files in [order_files/](order_files/README.txt), one folder per shop:

   | Shop | What it makes | Folder |
   |---|---|---|
   | JLCPCB | both circuit boards in one panel, black solder mask, all small parts mounted on both sides (with the new buck, protection IC and MOSFET) | `1_JLCPCB` |
   | JLCCNC + JLC3DP, one merged order | the aluminium tray and lid (black anodised, no marking), the PMMA kit with the clear main keys and the POM-C kit (JLCCNC); once per builder the two resin plates of the casting mould (JLC3DP) | `2_JLCCNC`, `3_rubber_keys` |
   | you | the two rubber side keys, cast in the mould, with a stainless plate and doubler glued in | `3_rubber_keys` |

   Shops that take small parts can make the PMMA and POM-C parts from the single files in
   `2_JLCCNC`.
3. Buy the remaining parts from the workbook [FlashKa_Parts_List_v0.7.xlsx](FlashKa_Parts_List_v0.7.xlsx):
   the 14500 cell (a Vapcell INR14500 F15 from an EU battery shop) with 0.2 mm pure nickel strip
   for its tabs, the LED board (SST-20 Gen 2 on a 10 mm copper board), the TIR optic (a pack of 5
   from an electronics distributor), the laser module, the M1.6 × 6 lid screws, the two M1.6 × 2.5
   pan-head key-board screws and the M1.6 × 5 laser set screw, two silicone hold-down pads, 24 AWG
   wire, thermal paste, polyimide tape, 0.5 mm foam, two-part epoxy for the optic and other
   adhesives, the casting supplies (ECON 80 urethane rubber, pigment, mould release, 0.3 mm
   stainless shim, glue) and, once per builder, four M3 × 16 bolts with washers and nuts for the
   resin mould. Unless the cell comes with welded tabs you also need a small spot welder: never
   solder onto the cell. Every part has a price, a link and its fees; the notes are in
   [docs/bom_notes.md](docs/bom_notes.md). Buy only a Class 2 laser module (1 mW or less):
   [LAS-1](../../docs/design-rules.md#las-1).
4. Cast the side keys, weld the strips onto the cell, install the firmware with the
   [installer](../flashka-keychain-v06/app/flashka-flasher.html) (choose "FlashKa v0.7"; Chrome or
   Edge on a computer), put the keys and the key board into the floor, test in the open tray, glue
   the optic over the LED board in the head, assemble and use the light as the guide says.

Ask JLCCNC whether it accepts the two machining kits (the parts hang on small tabs) and whether it
can cut the 0.2 mm panel texture; the parts work without the texture, which is a priced option in
the workbook.

## Cost

Prices as of 2026-10-23 (readings of parts that did not change: 2026-10-14, 2026-10-18,
2026-10-21 and 2026-10-22), delivered to Lithuania (EU, 21 % VAT), from the workbook and
[docs/bom_notes.md](docs/bom_notes.md):

| USD (EUR) | 1 light | 2 lights (total) | 5 lights (total) |
|---|---|---|---|
| PCB + assembly (JLCPCB, one panel), before shipping | 236.90 (211.74) | 236.90 (211.74) | 282.07 (252.11) |
| Housing (JLCCNC + JLC3DP: aluminium tray and lid, PMMA and POM-C kits, resin casting mould) | 132.91 (118.79) | 204.99 (183.23) | 432.50 (386.58) |
| Bought parts (the cell, LED board, TIR optic, laser, screws, ring, mould hardware) | 65.79 (58.80) | 95.75 (85.58) | 203.00 (181.44) |
| Consumables (nickel strip, wire, paste, tapes, foam, pads, adhesives, casting supplies) | 115.53 (103.26) | 115.53 (103.26) | 115.53 (103.26) |
| Shipping, VAT, customs duty, carrier and card fees | 308.16 (275.44) | 361.75 (323.34) | 463.25 (414.06) |
| **Total** | **859.28 (768.04)** | **1,014.92 (907.15)** | **1,496.35 (1,337.46)** |
| **Per light** | **859.28 (768.04)** | **507.46 (453.58)** | **299.27 (267.49)** |
| Tools, once (a spot welder for the cell's strips included) | about 204 (182) | | |

**What changed since the first v0.7 layout.** Against the workbook of the first v0.7 layout
(price check 2026-10-21; same scenarios and exchange rate):

| USD | 1 light | 2 lights | 5 lights |
|---|---|---|---|
| Per light, first v0.7 layout | 918.89 | 532.04 | 311.16 |
| Per light, now | 859.28 | 507.46 | 299.27 |
| **Change per light** | **−59.61** | **−24.58** | **−11.89** |
| Housing (total) | 169.16 → 132.91 | 242.46 → 204.99 | 473.59 → 432.50 |
| Consumables (total) | 142.19 → 115.53 | 142.19 → 115.53 | 142.19 → 115.53 |
| Shipping, VAT, customs, fees (total) | 315.13 → 308.16 | 349.12 → 361.75 | 452.61 → 463.25 |
| PCB + assembly (total) | 228.66 → 236.90 | 228.66 → 236.90 | 269.12 → 282.07 |
| Bought parts (total) | 63.75 → 65.79 | 101.65 → 95.75 | 218.30 → 203.00 |

The savings and what they cost in quality: the **resin casting mould** printed by JLC3DP (3.32 USD
instead of 35.12 USD for the aluminium mould) holds looser tolerances and wears sooner, so try the
first key in its opening; **ECON 80** instead of PMC-780 DRY (85.95 USD instead of 114.40 USD for
all casting supplies) has the same Shore 80A hardness and needs no scale, only a shorter pot life;
the **merged JLCCNC + JLC3DP parcel** of one light (EUR 118.79) stays below the EUR 150 customs
line and so pays no duty and no carrier fee (21.31 USD less), at no cost in quality; **no window and
no spacer ring**, because the optic is the window; a **cheaper LED board** (2.99 USD instead of
5.40 USD) that is also the better Gen 2 LED; thermal paste instead of tape and two AliExpress
parcels less. The optic (17.37 USD for five plus the distributor's parcel), the power stage and the
24 AWG wire add cost back. For two and five lights the parcels are above the customs line anyway,
so the saving per light is smaller. More options that trade quality for cost (no panel texture,
economy shipping, a cheaper pogo pin, Sugru instead of urethane) are priced in the workbook and in
[bom_notes.md, section 2.3](docs/bom_notes.md#23-options-what-else-would-save-money-and-what-it-costs);
together they would bring one light to about 712.15 USD.

**What the battery and body change costs.** Against the same workbook just before the change, with
two 320 mAh pouch cells in the 20 × 16 mm body (price check 2026-10-22):

| USD | 1 light | 2 lights | 5 lights |
|---|---|---|---|
| Per light, two pouch cells | 854.81 | 508.47 | 303.62 |
| Per light, one 14500 cell in the octagon | 859.28 | 507.46 | 299.27 |
| **Change per light** | **+4.47** | **−1.01** | **−4.35** |

The F15 costs 3.47 USD (read at nkon.nl) against an estimated 5.00 USD for each pouch cell, and one
cell replaces two: the bought parts drop by 8.06 USD for one light. The bigger tray and lid
(+1.02 USD), the nickel strip (+2.08 USD) and the battery shop's own parcel (an estimated
13.43 USD courier fee plus VAT, one web-shop parcel less) add more than that back for one light;
from two lights on the change saves money. A small spot welder (about 40 USD, a one-time tool, not
in the totals) is needed unless the cell comes with welded tabs. Details:
[bom_notes.md, section 2.2](docs/bom_notes.md#22-what-the-battery-and-body-change-costs).

One light is expensive because the fixed costs are paid once, whatever the quantity: JLCPCB's
assembly fees (145.15 USD: set-up for two board sides 51.12, feeder loading for 35 kinds of parts
53.55, stencils 16.42, X-ray inspection 13.12, the panel fee 8.21, the rest 2.73), the casting
supplies (85.95 USD, once per builder: one rubber kit casts many keys) and the resin mould
(3.32 USD), and shipping, VAT and fees (36 % of the total for one light). A builder who already
has the mould and the casting supplies pays 746.37 USD for one light. Building several lights at
once is the biggest saving.

Version 0.6 cost 620.21 USD for one light. The 239.07 USD difference: the casting supplies and the
other consumables (+87.74), shipping, VAT and customs (+69.38), the circuit boards (+62.57: the key
board, six pogo pins, the power stage, the panel fee and the two-design surcharge), the housing
(+10.35: the octagonal body, the two plastic kits and the mould replace the stainless caps, the
print kit and the laser marking) and the bought parts (+9.04: the optic, the 14500 cell, the new
screws and the mould hardware).

**Many prices are estimates.** The aluminium parts, the two plastic kits, the resin mould, the
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
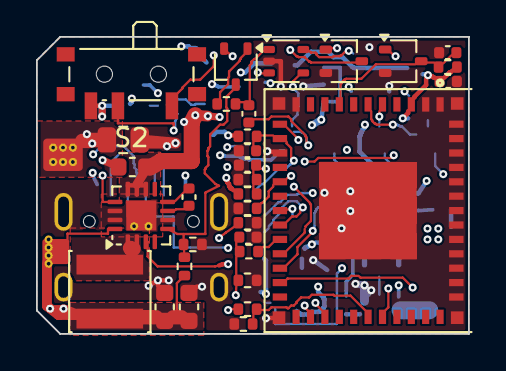
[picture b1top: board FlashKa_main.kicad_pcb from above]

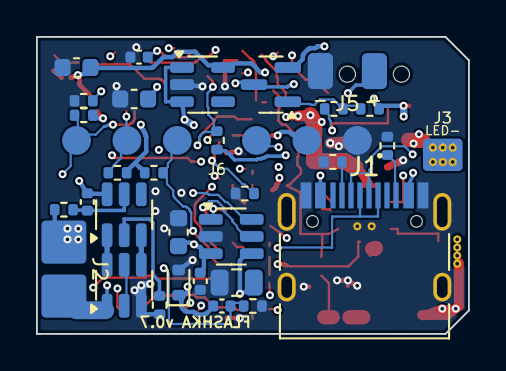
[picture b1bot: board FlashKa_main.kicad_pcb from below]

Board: 4 copper layers, 24.0 x 16.5 mm, 64 parts (31 on the bottom side), 44 nets.

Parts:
C1: 10uF; C_0805_2012Metric
C2, C13, C15: 10uF; C_0603_1608Metric
C5, C8, C22: 22uF; C_0603_1608Metric
C10, C16, C19, C20, C24: 100nF; C_0402_1005Metric
C11, C23: 10nF; C_0402_1005Metric
C12, C14, C17, C18: 1uF; C_0402_1005Metric
D1: ESD5Z5.0T1G; D_SOD-523
J1: TYPE-C-31-M-12; USB_C_Receptacle_HRO_TYPE-C-31-M-12
J2: CELL; WirePad_SMD_2_P3.0mm_24AWG
J3: LED; WirePad_LED_Split_24AWG
J5: LASER; WirePad_SMD_2_P3.0mm_N
J6: KB contacts; PogoTarget_6_D1.6_FlashKa
L1: 1uH; L_Changjiang_FNR4020S
Q1: AO3401A; SOT-23
Q2, Q4, Q5: 2N7002W; SOT-323_SC-70
Q3: SE8830A; SOT-23-6
R1, R2: 5.1k; R_0402_1005Metric
R3: 2k; R_0402_1005Metric
R7, R11, R15, R17, R20, R26, R29: 100k; R_0402_1005Metric
R8, R9, R13, R18, R21, R22: 10k; R_0402_1005Metric
R10: 200k; R_0402_1005Metric
R12: 47k; R_0402_1005Metric
R14, R16: 2.2k; R_0402_1005Metric
R19, R36: 1k; R_0402_1005Metric
R27, R28: 1M; R_0402_1005Metric
R35: 100Ω; R_0402_1005Metric
RS1: 20mΩ; R_0805_2012Metric
RT1: 100k B4250; R_0402_1005Metric
S2: MSK12C02; SW_SPDT_PCM12
U1: TP4057; SOT-23-6
U2: TPS62095RGTR; VQFN-16-1EP_3x3mm_P0.5mm_EP1.68x1.68mm_TV2
U3: TLV333IDCKR; SOT-353_SC-70-5
U4: ESP32-C3-MINI-1-N4; ESP32-C3-MINI-1
U5: RT9080-33GJ5; TSOT-23-5
U6: DW01A; SOT-23-6

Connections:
3V3: C15.1, C16.1, J6.2, R8.1, R9.1, R21.1, R22.1, R26.1, U4.3, U5.5
BATN: C24.2, J2.2, Q3.1, U6.6
BTN: J6.6, R9.2, U4.6, U4.23
BUCK_CN: C23.2, U2.8
BUCK_CP: C23.1, U2.7
CC1: J1.A5, R1.1
CC2: J1.B5, R2.1
CHG_DONE: U1.5, U4.19
CHG_SET: R3.2, R29.1, U4.30
CHG_STAT: U1.1, U4.18
EN: C18.1, Q5.3, R8.2, U4.8
FB: Q2.3, R10.2, R11.1, U2.5
GND: C1.2, C2.2, C5.2, C8.2, C10.2, C12.2, C13.2, C14.2, C15.2, C16.2, C18.2, C19.2, C20.2, C22.2, D1.2, J1.A1, J1.A12, J1.B1, J1.B12, J1.S1, J5.2, J6.1, Q3.3, Q4.2, Q5.2, R1.2, R2.2, R7.2, R11.2, R12.2, R16.2, R17.2, R20.2, R28.2, R29.2, R36.2, RS1.2, RT1.2, U1.2, U2.6, U2.14, U2.15, U2.17, U3.2, U4.1, U4.2, U4.11, U4.14, U4.36, U4.37, U4.38, U4.39, U4.40, U4.41, U4.42, U4.43, U4.44, U4.45, U4.46, U4.47, U4.48, U4.49, U4.50, U4.51, U4.52, U4.53, U5.2
INV: C11.1, R14.2, U3.4
ISNS: J3.2, R14.1, RS1.1
LASER_N: Q4.3, S2.1
LASER_ON: Q4.1, R20.1, U4.16
LASER_P: C13.1, J5.1, Q1.3
LED_EN: C10.1, R17.1, U2.13, U3.5, U4.21
LED_PWM: R15.1, U4.20
NTC_ADC: C19.1, R26.2, RT1.1, U4.13
PROG: R3.1, U1.6
PROT_CS: R36.1, U6.2
PROT_D: Q3.2, Q3.5
PROT_OC: Q3.4, U6.3
PROT_OD: Q3.6, U6.1
PROT_VCC: C24.1, R35.2, U6.5
QG: Q2.1, R13.2
QL_G: Q1.1, R18.1, R19.1
QS: Q2.2, R12.1
RGB_B: J6.5, R22.2, U4.5
RGB_G: J6.4, R21.2, U4.22
RGB_R: J6.3, U4.31
RST_G: C17.2, Q5.1, R7.1
S2_COM: R19.2, S2.2
SW: L1.1, U2.1, U2.2
USB_DN: J1.A7, J1.B7, U4.26
USB_DP: J1.A6, J1.B6, U4.27
VBAT: C2.1, C5.1, C14.1, J2.1, Q1.2, R18.2, R27.1, R35.1, S2.3, U1.3, U2.3, U2.10, U2.11, U2.12, U5.1, U5.3
VBAT_ADC: C20.1, R27.2, R28.1, U4.12
VBUS: C1.1, C17.1, D1.1, J1.A4, J1.A9, J1.B4, J1.B9, U1.4
VC: C11.2, R13.1, U3.1
VOUT: C8.1, C22.1, J3.1, L1.2, R10.1, U2.16
VSET: C12.1, R15.2, R16.1, U3.3

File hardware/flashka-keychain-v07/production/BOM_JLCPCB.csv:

Comment,Designator,Footprint,LCSC Part #,Quantity
10uF,C1,C_0805_2012Metric,C15850,1
10uF,"C2,C13,C15",C_0603_1608Metric,C19702,3
22uF,"C5,C8,C22",C_0603_1608Metric,C59461,3
1uF,"C12,C14,C17,C18",C_0402_1005Metric,C52923,4
10nF,"C11,C23",C_0402_1005Metric,C15195,2
100nF,"C10,C16,C19,C20,C24",C_0402_1005Metric,C1525,5
ESD5Z5.0T1G,D1,D_SOD-523,C82044,1
TYPE-C-31-M-12,J1,USB_C_Receptacle_HRO_TYPE-C-31-M-12,C165948,1
1uH,L1,L_Changjiang_FNR4020S,C602028,1
NH-B1010RGBT-HF,"LED3,LED4",LED_RGB_1010_NH-B1010RGBT,C2874113,2
P70-1010045R,"P1,P2,P3,P4,P5,P6",Pogo_Harwin_P70-1010045R,C22100007,6
AO3401A,Q1,SOT-23,C15127,1
SE8830A,Q3,SOT-23-6,C238645,1
2N7002W,"Q2,Q4,Q5",SOT-323_SC-70,C5224240,3
5.1k,"R1,R2",R_0402_1005Metric,C25905,2
2k,R3,R_0402_1005Metric,C4109,1
200k,R10,R_0402_1005Metric,C25764,1
47k,R12,R_0402_1005Metric,C25792,1
10k,"R8,R9,R13,R18,R21,R22",R_0402_1005Metric,C25744,6
2.2k,"R14,R16,R31",R_0402_1005Metric,C25879,3
330Ω,"R23,R32",R_0402_1005Metric,C25104,2
1M,"R27,R28",R_0402_1005Metric,C26083,2
100k,"R7,R11,R15,R17,R20,R26,R29",R_0402_1005Metric,C25741,7
100Ω,"R24,R25,R33,R34,R35",R_0402_1005Metric,C25076,5
1k,"R19,R30,R36",R_0402_1005Metric,C11702,3
20mΩ,RS1,R_0805_2012Metric,C92740,1
100k B4250,RT1,R_0402_1005Metric,C77130,1
MSK12C02,S2,SW_SPDT_PCM12,C431540,1
SKRKAEE020,"SW1,SW2,SW3",SW_Push_SPST_NO_Alps_SKRK,C115357,3
TP4057,U1,SOT-23-6,C12044,1
TPS62095RGTR,U2,VQFN-16-1EP_3x3mm_P0.5mm_EP1.68x1.68mm_TV2,C139643,1
TLV333IDCKR,U3,SOT-353_SC-70-5,C181502,1
ESP32-C3-MINI-1-N4,U4,ESP32-C3-MINI-1,C2838502,1
RT9080-33GJ5,U5,TSOT-23-5,C841192,1
DW01A,U6,SOT-23-6,C351410,1

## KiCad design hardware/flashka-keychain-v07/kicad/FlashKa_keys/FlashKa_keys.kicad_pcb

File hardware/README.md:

<!-- SPDX-License-Identifier: CC-BY-SA-4.0 -->
[LuxLibre](../README.md) › Lights

# The lights

LuxLibre's reference designs: complete, editable lights that follow the [design rules](../docs/design-rules.md) and
run the LuxLibre firmware. Each folder can be built without anything else from this repository. None of them has
been built yet: every picture is a render and every light figure is simulated or estimated.

<picture>
  <source media="(prefers-color-scheme: dark)" srcset="../docs/img/lineup_dark.png">
  
</picture>

## Current designs

<table>
<tr>
<td width="33%" valign="top">

<h3><a href="flashka-keychain-v07/README.md">FlashKa v0.7</a></h3>
Keychain light with a laser and a Bluetooth presenter mode. 99.2 × 20 × 18 mm, one 14500, about 1,045 lm.<br>
<sub>Boards drawn, order files ready; not yet built. <a href="flashka-keychain-v07/cad/README.md">Drawings</a> · <a href="flashka-keychain-v07/assets/v07/README.md">Pictures</a> · <a href="flashka-keychain-v07/FlashKa_v0.7_Build_Guide.pdf">Build guide</a></sub>
</td>
<td width="33%" valign="top">

<h3><a href="edco-prism/README.md">EDCO Prism</a></h3>
A beam that is white or any colour. Ø28 × 83 mm, one 18350, about 1,250 lm.<br>
<sub>Concept: housing done, boards not drawn. <a href="edco-prism/cad/README.md">Drawings</a> · <a href="edco-prism/assets/README.md">Pictures</a> · <a href="../firmware/boards/edco-prism/board.h">Firmware</a></sub>
</td>
<td width="33%" valign="top">

<h3><a href="edco-mini/README.md">EDCO Mini</a></h3>
Sealed keychain light with red and UV side lights. Ø22 × 73.5 mm (16340) or Ø19 × 69.4 mm, about 950 lm.<br>
<sub>Concept: housing done, boards not drawn. <a href="edco-mini/cad/README.md">Drawings</a> · <a href="edco-mini/assets/README.md">Pictures</a> · <a href="../firmware/boards/edco-mini-16/board.h">Firmware</a></sub>
</td>
</tr>
<tr>
<td width="33%" valign="top">

<h3><a href="edco-v02/README.md">EDCO v0.2</a></h3>
The bright one: an SST-40 at up to 5.7 A, about 1,760 lm. EDCO-18 (Ø26 × 97.8 mm) or EDCO-14 (Ø22 × 95.6 mm).<br>
<sub>Concept: housing done, boards not drawn. <a href="edco-v02/cad/README.md">Drawings</a> · <a href="edco-v02/assets/README.md">Pictures</a> · <a href="../firmware/boards/edco-v02-18/board.h">Firmware</a></sub>
</td>
<td width="33%" valign="top">

<h3><a href="edco-v01/README.md">EDCO v0.1</a></h3>
A plain sealed tube with USB-C in the tail. Ø20 × 93.5 mm, one 14500, about 966 lm.<br>
<sub>Concept: housing done, boards not drawn. <a href="edco-v01/cad/README.md">Drawings</a> · <a href="edco-v01/assets/README.md">Pictures</a> · <a href="../firmware/boards/edco-v01/board.h">Firmware</a></sub>
</td>
<td width="33%" valign="top">
<h3><a href="../docs/comparison.md">How they compare</a></h3>
Every design against 14 popular lights of the same cell size: light at 30 s and after 10 minutes, throw, runtime,
size and price, with the reviewers' measurements and sources.<br><br>
<h3><a href="../templates/README.md">Make your own</a></h3>
Start from the requirement sheet and the <a href="../docs/README.md">design guide</a>, then see
<a href="#adding-a-design">Adding a design</a> below.
</td>
</tr>
</table>

## Older designs

| Design | What it is |
|---|---|
| [FlashKa v0.6](flashka-keychain-v06/README.md) | the previous FlashKa: three buttons with a glowing ring, the presenter mode. Its folder also holds the FlashKa firmware of v0.6 and v0.7 and the web pages |
| [FlashKa v0.5](flashka-keychain-v05/README.md) | the first FlashKa: two LiPo pouch cells, an SST-20 at up to 2.2 A, a Class 2 laser, USB-C and Bluetooth |

## What is in a design folder

Every design folder has the same layout, so once you know one you know them all.

| Path | What is in it |
|---|---|
| `README.md` | the design page: what the light is, specifications, simulated light and runtime, how it is built, cost, checks, open points |
| `cad/` | drawings (PDF, DXF, PNG) and 3D models (STEP), with a README that shows every sheet |
| `assets/` | renders and animations, with a README gallery |
| `tools/housing/` | the scripts that make the CAD, the checks and the renders |
| [`../firmware/boards/<name>/`](../firmware/boards/README.md) | the light's firmware board header |

The FlashKa folders also have `kicad/` (the circuit boards), `production/` (Gerbers, BOM, placement), `order_files/`
(upload-ready files for the shops), `docs/` (build guide and notes), the build guide and hardware package PDFs and
the parts and cost workbook.

## Shared tools

The drawings, animations, lineup, banner and folder pages of the EDCO designs are made by the scripts in
[tools/](tools/README.md).

## Adding a design

A reference design folder contains:

- `README.md`: what it is, specifications, status, how to build it, cost, known limitations,
  licences (use the FlashKa README as the pattern);
- editable sources: schematic and PCB (KiCad preferred), mechanical CAD as STEP plus the native
  files or generator scripts, drawings with tolerances ([MEC-8](../docs/design-rules.md#mec-8));
- production files: Gerbers, drill, BOM with manufacturer part numbers, pick-and-place
  ([DFM-7](../docs/design-rules.md#dfm-7));
- the LuxLibre board header in `firmware/boards/<name>/` ([FW-2](../docs/design-rules.md#fw-2));
- the filled requirement sheet, design log and review checklist
  ([templates/](../templates/README.md));
- test reports once it has been built ([docs/testing.md](../docs/testing.md)).

Design files are licensed CERN-OHL-W-2.0, scripts GPL-3.0-or-later, documents CC-BY-SA-4.0
([LICENSING.md](../LICENSING.md)).

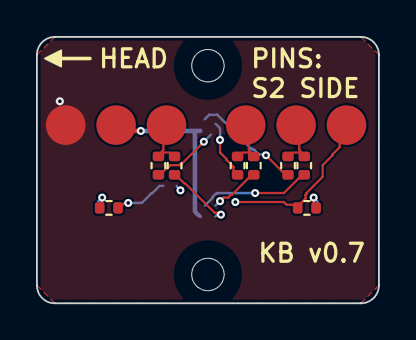
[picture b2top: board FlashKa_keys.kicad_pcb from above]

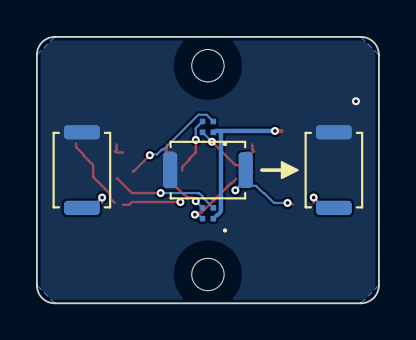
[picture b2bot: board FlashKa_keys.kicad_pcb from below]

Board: 4 copper layers, 19.0 x 14.8 mm, 21 parts (5 on the bottom side), 14 nets.

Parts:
H1, H2: M1.6; MountingHole_1.8mm_M1.6
LED3, LED4: NH-B1010RGBT-HF; LED_RGB_1010_NH-B1010RGBT
P1, P2, P3, P4, P5, P6: P70-1010045R; Pogo_Harwin_P70-1010045R
R23, R32: 330Ω; R_0402_1005Metric
R24, R25, R33, R34: 100Ω; R_0402_1005Metric
R30: 1k; R_0402_1005Metric
R31: 2.2k; R_0402_1005Metric
SW1, SW2, SW3: SKRKAEE020; SW_Push_SPST_NO_Alps_SKRK

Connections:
3V3: LED3.1, LED4.1, P2.1
BTN: P6.1, R30.1, R31.1, SW1.1
BTN_NX: R30.2, SW2.1
BTN_PV: R31.2, SW3.1
B_K: LED3.4, R25.1
B_K2: LED4.4, R34.1
GND: P1.1, SW1.2, SW2.2, SW3.2
G_K: LED3.3, R24.1
G_K2: LED4.3, R33.1
RGB_B: P5.1, R25.2, R34.2
RGB_G: P4.1, R24.2, R33.2
RGB_R: P3.1, R23.2, R32.2
R_K: LED3.2, R23.1
R_K2: LED4.2, R32.1

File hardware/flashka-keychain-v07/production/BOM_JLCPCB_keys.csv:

Comment,Designator,Footprint,LCSC Part #,Quantity
NH-B1010RGBT-HF,"LED3,LED4",LED_RGB_1010_NH-B1010RGBT,C2874113,2
P70-1010045R,"P1,P2,P3,P4,P5,P6",Pogo_Harwin_P70-1010045R,C22100007,6
330Ω,"R23,R32",R_0402_1005Metric,C25104,2
100Ω,"R24,R25,R33,R34",R_0402_1005Metric,C25076,4
1k,R30,R_0402_1005Metric,C11702,1
2.2k,R31,R_0402_1005Metric,C25879,1
SKRKAEE020,"SW1,SW2,SW3",SW_Push_SPST_NO_Alps_SKRK,C115357,3

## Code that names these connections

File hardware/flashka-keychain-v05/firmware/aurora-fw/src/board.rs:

// SPDX-License-Identifier: MIT OR Apache-2.0
//! ESP32-C3 pin map of the Aurora++ v0.5 main board.
//!
//! Mirrors `GPIO_MAP` in `tools/kicad/aurora_parts.py` (the single source of
//! truth for the hardware). Module pad numbers of the ESP32-C3-MINI-1 in brackets.
//!
//! | GPIO | Pad | Net | Use in firmware |
//! |---|---|---|---|
//! | 0 | 12 | VBAT_ADC | ADC1_CH0, 11 dB, curve calibration; VBAT = 2 x V |
//! | 1 | 13 | NTC_ADC | ADC1_CH1, 11 dB; 100 k to 3V3, NTC 100 k B4250 to GND |
//! | 2 | 5 | RGB_B | LEDC ch3, active low (strap, 10 k pull-up) |
//! | 3 | 6 | BTN | input, low = pressed; deep-sleep wake source |
//! | 4 | 18 | CHG_STAT | input + pull-up, low = charging; wake source |
//! | 5 | 19 | CHG_DONE | input + pull-up, low = charge complete; wake source |
//! | 6 | 20 | LED_PWM | LEDC ch0, 13 bit, 9.77 kHz -> current set point |
//! | 7 | 21 | LED_EN | output, high = LED driver + op-amp on (100 k pull-down) |
//! | 8 | 22 | RGB_G | LEDC ch2, active low (strap, 10 k pull-up) |
//! | 9 | 23 | BTN | boot strap, same button; never driven by the firmware |
//! | 10 | 16 | LASER_ON | output, high = laser on if S2 armed (100 k pull-down) |
//! | 18/19 | 26/27 | USB D-/D+ | USB-Serial-JTAG (console, flashing) - untouched |
//! | 20 | 30 | CHG_SET | low = ~300 mA, floating = 10 mA trickle, high = charger off |
//! | 21 | 31 | RGB_R | LEDC ch1, active low (U0TXD: ROM boot log flickers it) |

pub const GPIO_VBAT_ADC: u8 = 0;
pub const GPIO_NTC_ADC: u8 = 1;
pub const GPIO_RGB_B: u8 = 2;
pub const GPIO_BTN: u8 = 3;
pub const GPIO_CHG_STAT: u8 = 4;
pub const GPIO_CHG_DONE: u8 = 5;
pub const GPIO_LED_PWM: u8 = 6;
pub const GPIO_LED_EN: u8 = 7;
pub const GPIO_RGB_G: u8 = 8;
pub const GPIO_BTN_STRAP: u8 = 9;
pub const GPIO_LASER_ON: u8 = 10;
pub const GPIO_CHG_SET: u8 = 20;
pub const GPIO_RGB_R: u8 = 21;

/// GPIO output-register mask of the two outputs that must be low on every
/// fault path (used by the panic handler, which writes the register directly).
pub const SAFETY_OFF_MASK: u32 = (1 << GPIO_LED_EN) | (1 << GPIO_LASER_ON);

/// LEDC frequency of the LED current set point and the RGB channels: the
/// highest frequency with 13-bit resolution from the 80 MHz APB clock
/// (80 MHz / 8192 = 9765.6 Hz).
pub const PWM_FREQ_HZ: u32 = 9_765;

/// LEDC duty value for 100 % at 13 bits.
pub const PWM_FULL: u32 = 1 << 13;

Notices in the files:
hardware/flashka-keychain-v07/README.md:
Licences:
Hardware design files (KiCad, CAD, drawings and their PDFs, production files): CERN-OHL-W-2.0. The
Python generator scripts: GPL-3.0-or-later. The build guide, design chapter and other documents:
CC-BY-SA-4.0. The FlashKa Rust firmware, the web app and the web tools (in the v0.6 folder): MIT OR
Apache-2.0. Details and what they mean for building and selling FlashKa lights:
Previous design:** [FlashKa Keychain v0.6](../flashka-keychain-v06/README.md) (stainless buttons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
README.md:
https://img.shields.io/badge/firmware-GPL--3.0--or--later-blue
